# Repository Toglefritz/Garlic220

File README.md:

# Garlic220
The Garlic220 is an LED matrix for your NZXT H500 PC case featuring a 10 x 22 grid of WS2812B addressable LEDs (for 220 LEDs in total, hense the number in the name). The matrix, once mounted on a 3D printed frame with an acrylic diffuser, creates a grid of pixel-like lights. Using a bespoke Android app, the color of every pixel in the display can be controlled, allowing the Garlic220 to display any design you'd like.

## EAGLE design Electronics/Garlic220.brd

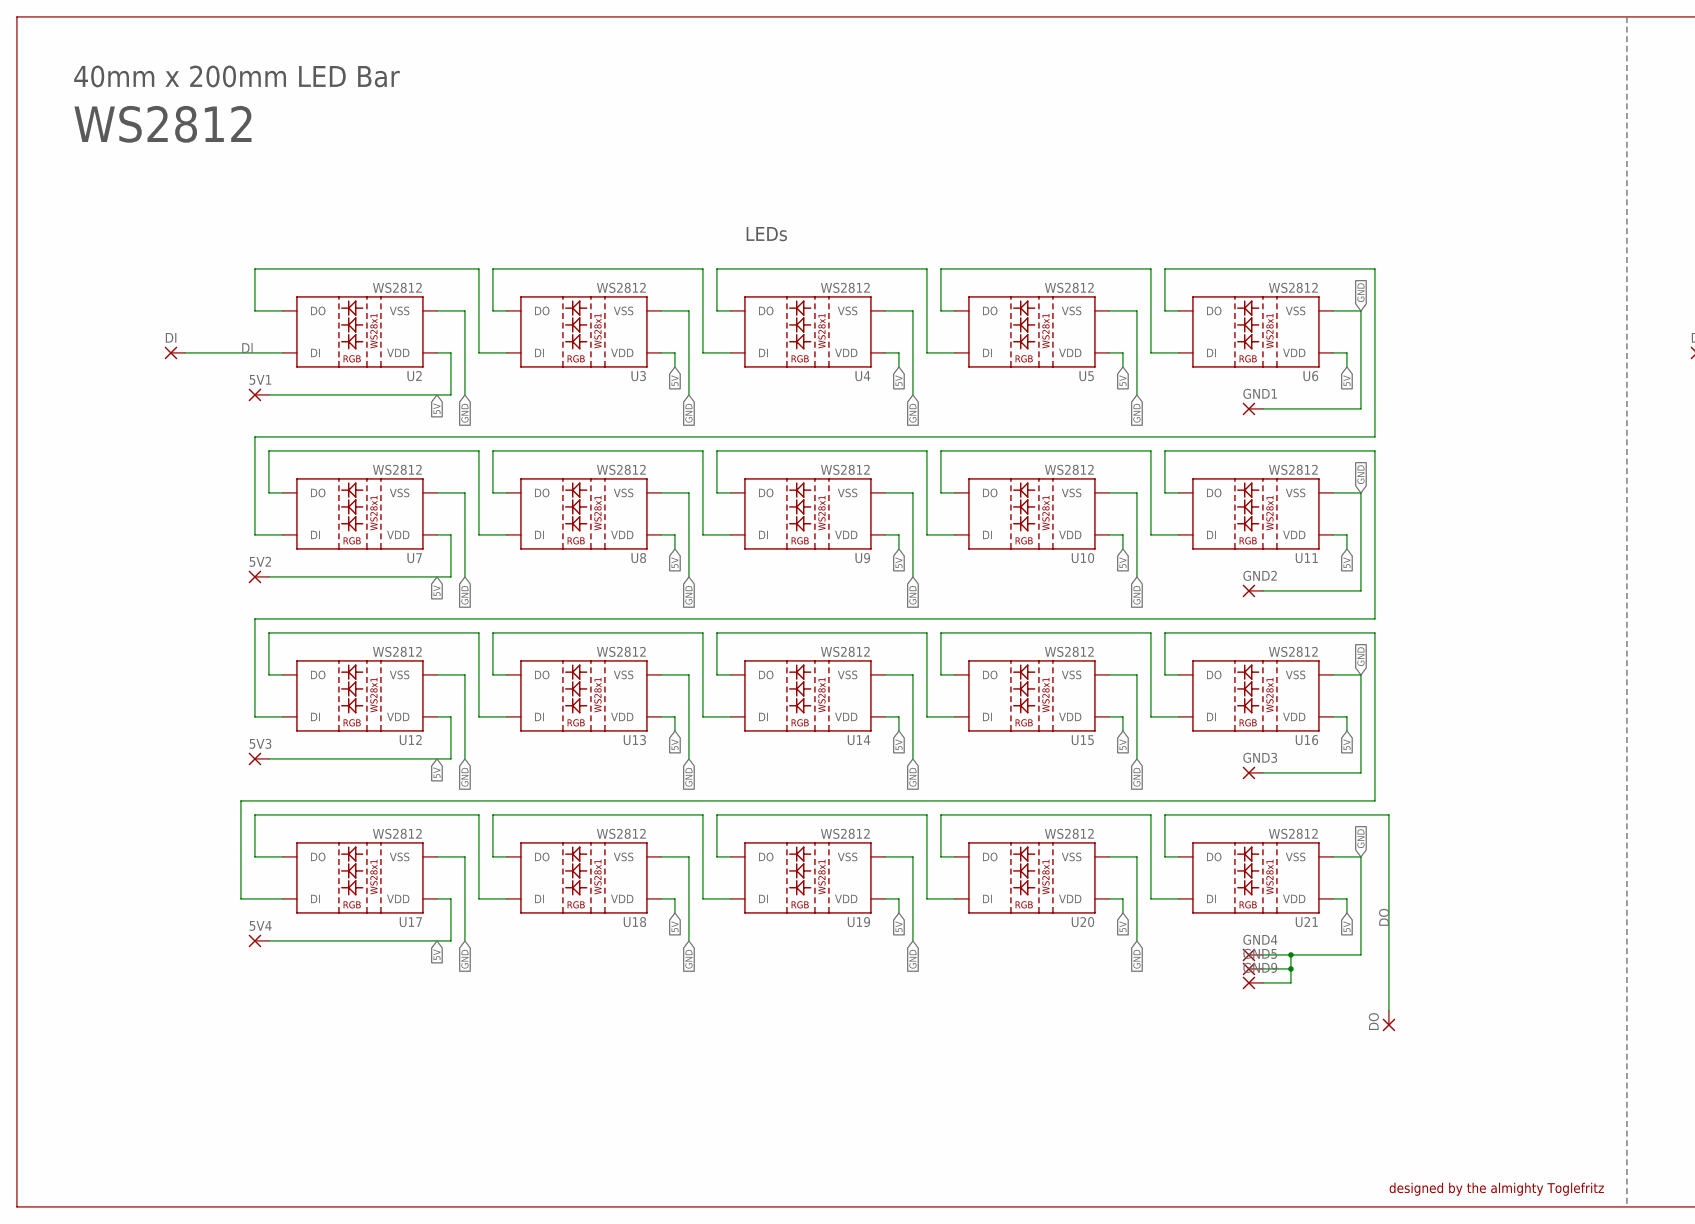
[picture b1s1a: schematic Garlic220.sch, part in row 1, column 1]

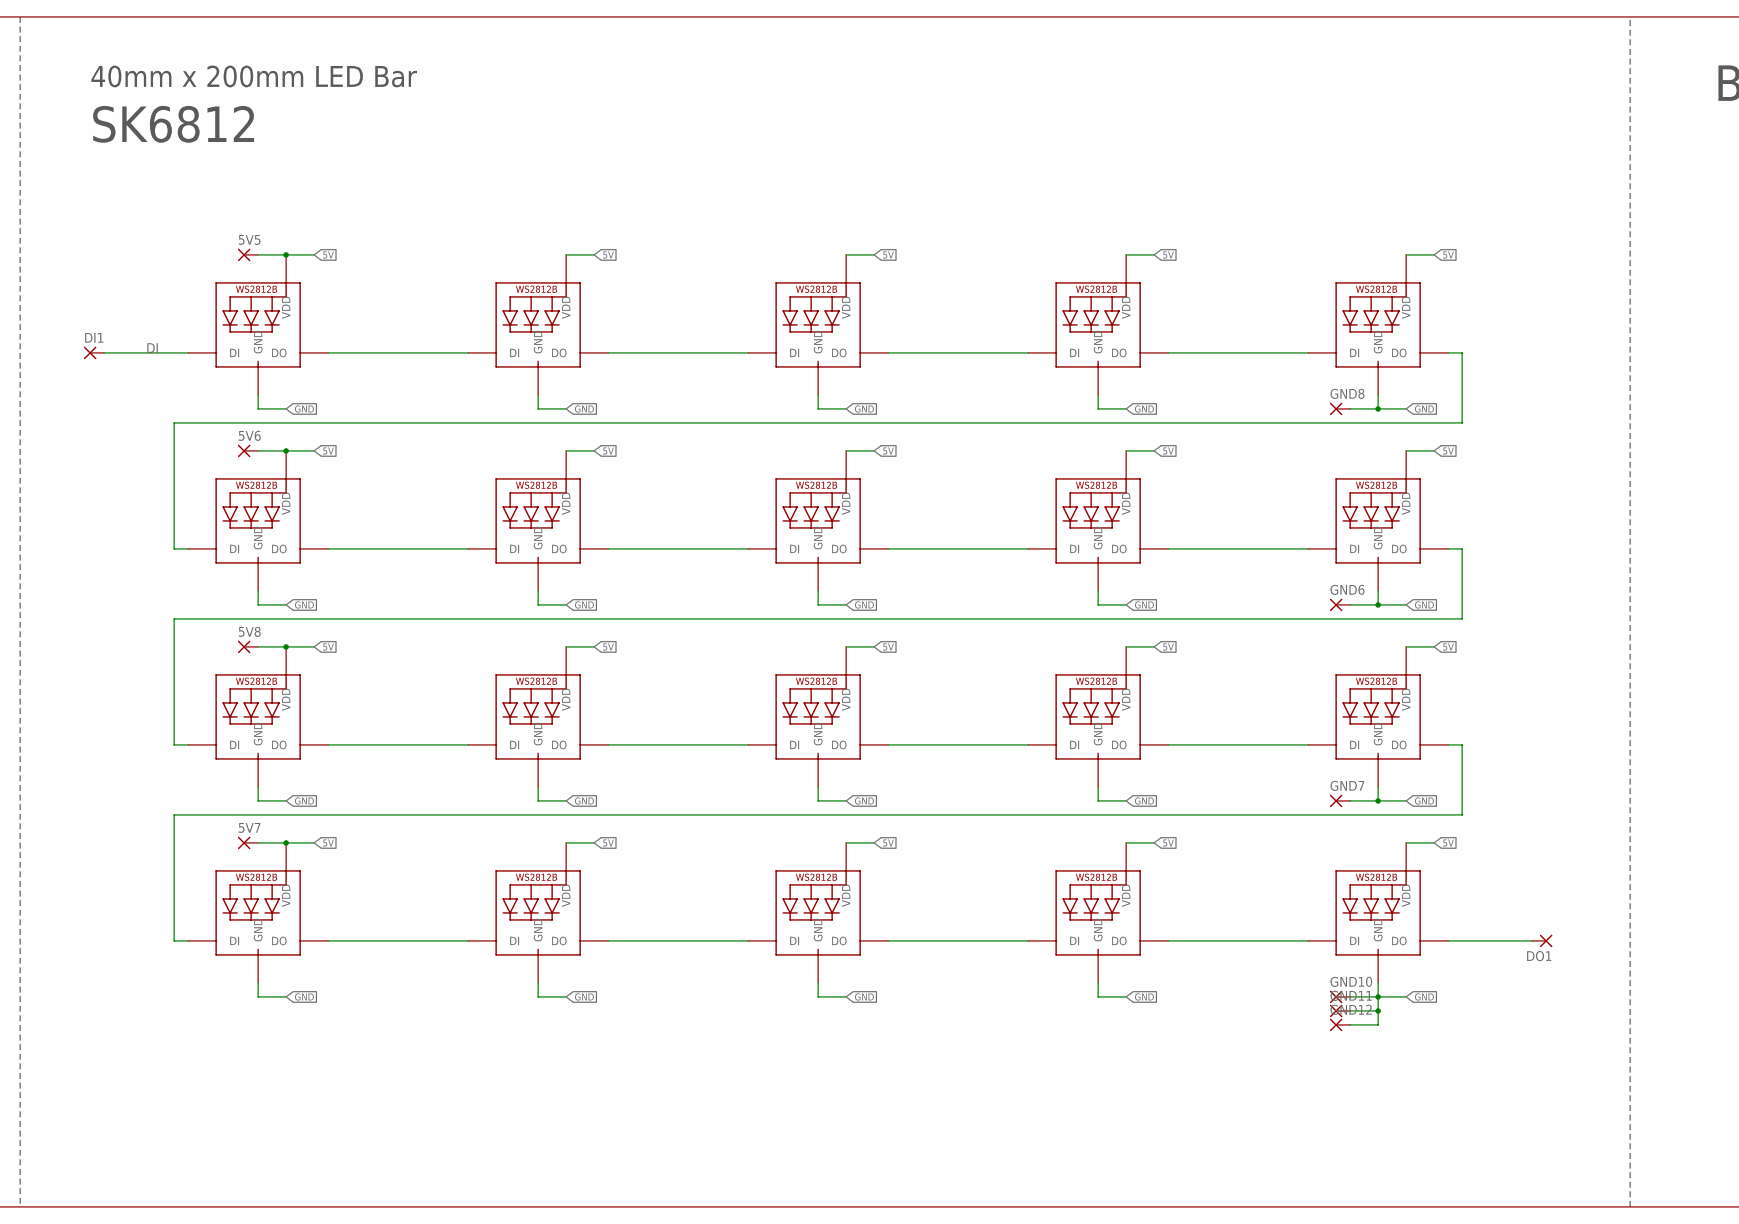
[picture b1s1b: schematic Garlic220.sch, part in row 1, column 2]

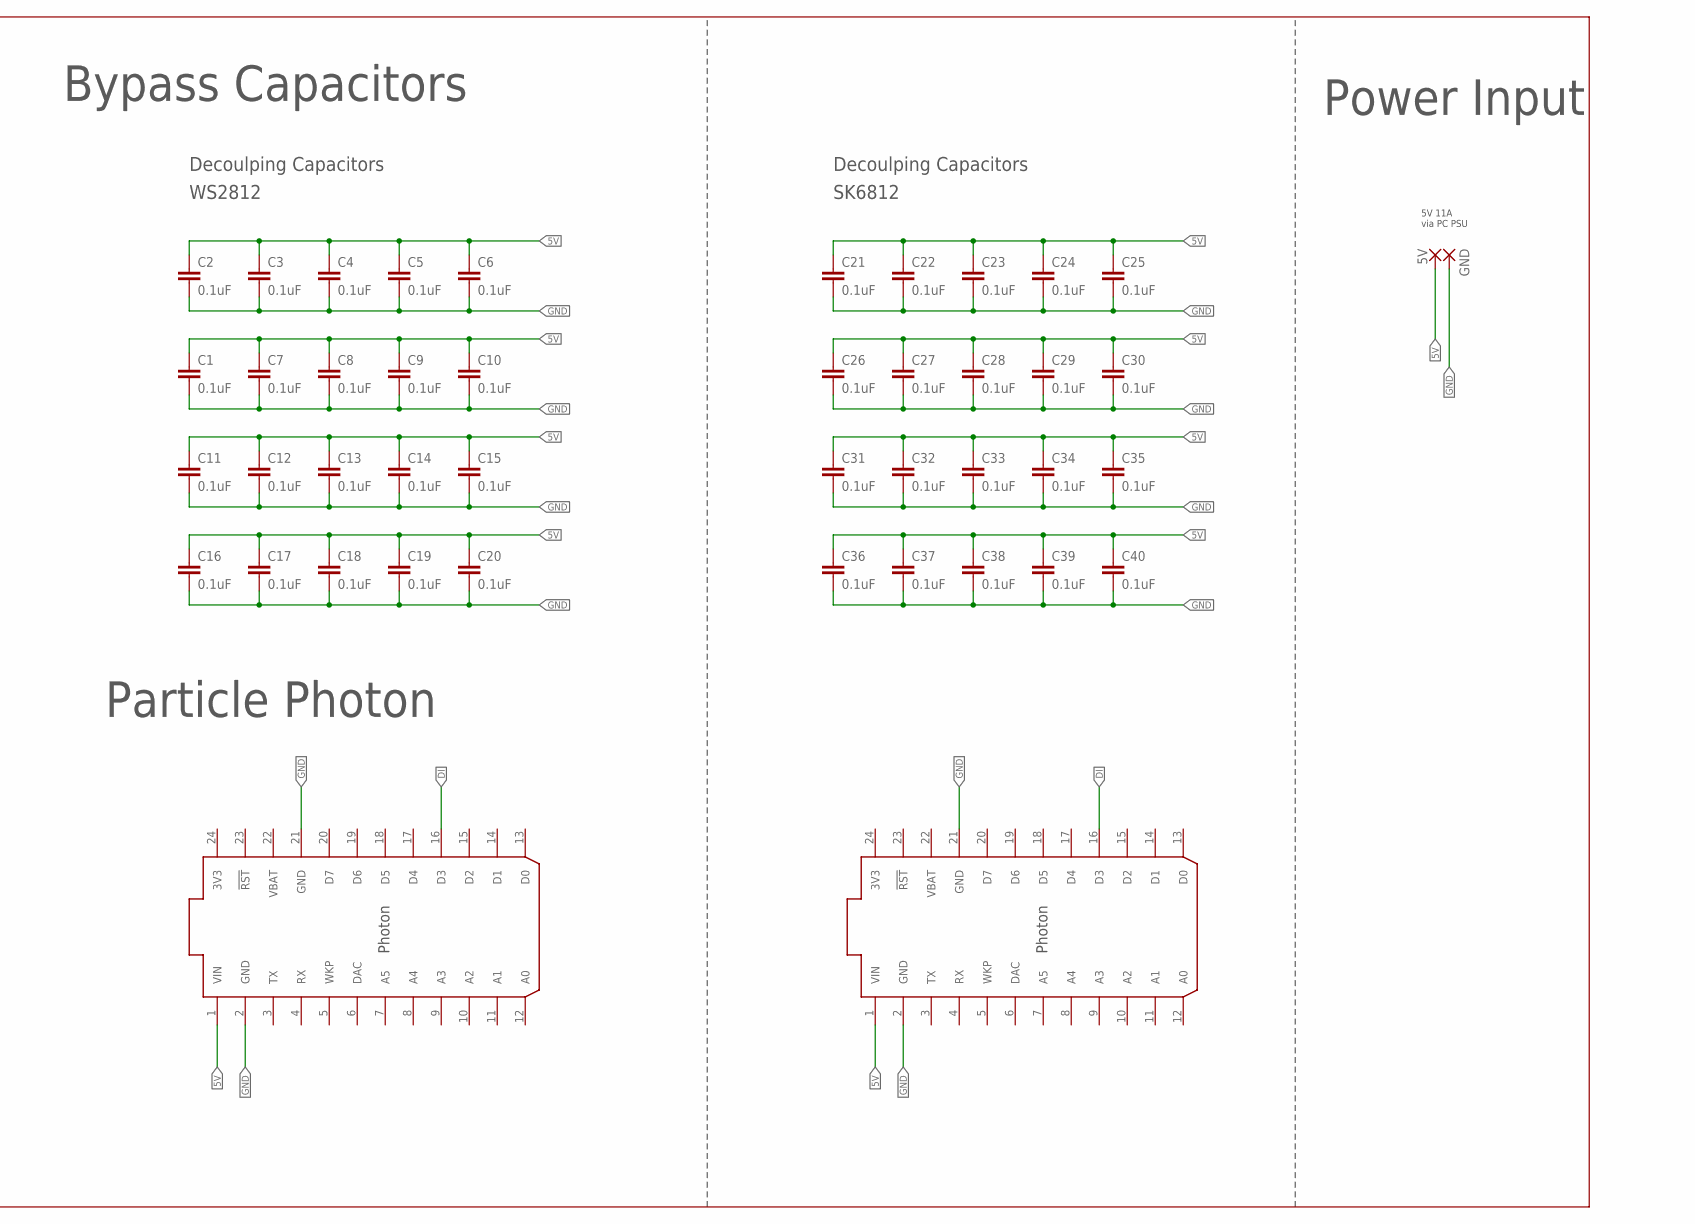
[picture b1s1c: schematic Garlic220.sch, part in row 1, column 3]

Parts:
5V: 3,81/1,1
5V1, 5V2, 5V3, 5V4, 5V5, 5V6, 5V7, 5V8: SMD5; SMD2,54-5,08
C1, C2, C3, C4, C5, C6, C7, C8, C9, C10, C11, C12, C13, C14, C15, C16, C17, C18, C19, C20, C21, C22, C23, C24, C25, C26, C27, C28, C29, C30, C31, C32, C33, C34, C35, C36, C37, C38, C39, C40: 0.1uF; 0805
DI, DI1: SMD5; SMD2,54-5,08
DO, DO1: SMD5; SMD2,54-5,08
GND: 3,81/1,1
GND1, GND2, GND3, GND4, GND5, GND6, GND7, GND8, GND9, GND10, GND11, GND12: SMD5; SMD2,54-5,08
LED21, LED22, LED23, LED24, LED25, LED26, LED27, LED28, LED29, LED30, LED31, LED32, LED33, LED34, LED35, LED36, LED37, LED38, LED39, LED40: WS2812B5050; WS2812B
U2, U3, U4, U5, U6, U7, U8, U9, U10, U11, U12, U13, U14, U15, U16, U17, U18, U19, U20, U21: WS2812; LED-TRICOLOR-5050-IC
U$1, U$2: PHOTON_SMD

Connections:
3V3: U$1.24 (3V3), U$2.24 (3V3)
5V: 5V.1, 5V1.1, 5V2.1, 5V3.1, 5V4.1, 5V5.1, 5V6.1, 5V7.1, 5V8.1, C1.1, C2.1, C3.1, C4.1, C5.1, C6.1, C7.1, C8.1, C9.1, C10.1, C11.1, C12.1, C13.1, C14.1, C15.1, C16.1, C17.1, C18.1, C19.1, C20.1, C21.1, C22.1, C23.1, C24.1, C25.1, C26.1, C27.1, C28.1, C29.1, C30.1, C31.1, C32.1, C33.1, C34.1, C35.1, C36.1, C37.1, C38.1, C39.1, C40.1, LED21.1-VDD (VDD), LED22.1-VDD (VDD), LED23.1-VDD (VDD), LED24.1-VDD (VDD), LED25.1-VDD (VDD), LED26.1-VDD (VDD), LED27.1-VDD (VDD), LED28.1-VDD (VDD), LED29.1-VDD (VDD), LED30.1-VDD (VDD), LED31.1-VDD (VDD), LED32.1-VDD (VDD), LED33.1-VDD (VDD), LED34.1-VDD (VDD), LED35.1-VDD (VDD), LED36.1-VDD (VDD), LED37.1-VDD (VDD), LED38.1-VDD (VDD), LED39.1-VDD (VDD), LED40.1-VDD (VDD), U2.3 (VDD), U2.5 (VDD), U3.3 (VDD), U3.5 (VDD), U4.3 (VDD), U4.5 (VDD), U5.3 (VDD), U5.5 (VDD), U6.3 (VDD), U6.5 (VDD), U7.3 (VDD), U7.5 (VDD), U8.3 (VDD), U8.5 (VDD), U9.3 (VDD), U9.5 (VDD), U10.3 (VDD), U10.5 (VDD), U11.3 (VDD), U11.5 (VDD), U12.3 (VDD), U12.5 (VDD), U13.3 (VDD), U13.5 (VDD), U14.3 (VDD), U14.5 (VDD), U15.3 (VDD), U15.5 (VDD), U16.3 (VDD), U16.5 (VDD), U17.3 (VDD), U17.5 (VDD), U18.3 (VDD), U18.5 (VDD), U19.3 (VDD), U19.5 (VDD), U20.3 (VDD), U20.5 (VDD), U21.3 (VDD), U21.5 (VDD), U$1.1 (VIN), U$2.1 (VIN)
DI: DI.1, DI1.1, LED21.4-DIN (DI), U2.2 (DI), U$1.16 (D3), U$2.16 (D3)
DI1: U16.1 (DO), U17.2 (DI)
DO: DO.1, U21.1 (DO)
GND: C1.2, C2.2, C3.2, C4.2, C5.2, C6.2, C7.2, C8.2, C9.2, C10.2, C11.2, C12.2, C13.2, C14.2, C15.2, C16.2, C17.2, C18.2, C19.2, C20.2, C21.2, C22.2, C23.2, C24.2, C25.2, C26.2, C27.2, C28.2, C29.2, C30.2, C31.2, C32.2, C33.2, C34.2, C35.2, C36.2, C37.2, C38.2, C39.2, C40.2, GND.1, GND1.1, GND2.1, GND3.1, GND4.1, GND5.1, GND6.1, GND7.1, GND8.1, GND9.1, GND10.1, GND11.1, GND12.1, LED21.3-GND (GND), LED22.3-GND (GND), LED23.3-GND (GND), LED24.3-GND (GND), LED25.3-GND (GND), LED26.3-GND (GND), LED27.3-GND (GND), LED28.3-GND (GND), LED29.3-GND (GND), LED30.3-GND (GND), LED31.3-GND (GND), LED32.3-GND (GND), LED33.3-GND (GND), LED34.3-GND (GND), LED35.3-GND (GND), LED36.3-GND (GND), LED37.3-GND (GND), LED38.3-GND (GND), LED39.3-GND (GND), LED40.3-GND (GND), U2.6 (VSS), U3.6 (VSS), U4.6 (VSS), U5.6 (VSS), U6.6 (VSS), U7.6 (VSS), U8.6 (VSS), U9.6 (VSS), U10.6 (VSS), U11.6 (VSS), U12.6 (VSS), U13.6 (VSS), U14.6 (VSS), U15.6 (VSS), U16.6 (VSS), U17.6 (VSS), U18.6 (VSS), U19.6 (VSS), U20.6 (VSS), U21.6 (VSS), U$1.2 (GND), U$1.21 (GND), U$2.2 (GND), U$2.21 (GND)
unnamed: U2.1 (DO), U3.2 (DI)
unnamed: U3.1 (DO), U4.2 (DI)
unnamed: U4.1 (DO), U5.2 (DI)
unnamed: U7.1 (DO), U8.2 (DI)
unnamed: U8.1 (DO), U9.2 (DI)
unnamed: U9.1 (DO), U10.2 (DI)
unnamed: U6.1 (DO), U7.2 (DI)
unnamed: U12.1 (DO), U13.2 (DI)
unnamed: U13.1 (DO), U14.2 (DI)
unnamed: U14.1 (DO), U15.2 (DI)
unnamed: U11.1 (DO), U12.2 (DI)
unnamed: U5.1 (DO), U6.2 (DI)
unnamed: U17.1 (DO), U18.2 (DI)
unnamed: U15.1 (DO), U16.2 (DI)
unnamed: U18.1 (DO), U19.2 (DI)
unnamed: U10.1 (DO), U11.2 (DI)
unnamed: U19.1 (DO), U20.2 (DI)
unnamed: LED21.2-DOUT (DO), LED22.4-DIN (DI)
unnamed: LED22.2-DOUT (DO), LED23.4-DIN (DI)
unnamed: LED23.2-DOUT (DO), LED24.4-DIN (DI)
unnamed: LED24.2-DOUT (DO), LED25.4-DIN (DI)
unnamed: LED25.2-DOUT (DO), LED26.4-DIN (DI)
unnamed: LED26.2-DOUT (DO), LED27.4-DIN (DI)
unnamed: LED27.2-DOUT (DO), LED28.4-DIN (DI)
unnamed: LED28.2-DOUT (DO), LED29.4-DIN (DI)
unnamed: U20.1 (DO), U21.2 (DI)
unnamed: LED29.2-DOUT (DO), LED30.4-DIN (DI)
unnamed: LED30.2-DOUT (DO), LED31.4-DIN (DI)
unnamed: LED31.2-DOUT (DO), LED32.4-DIN (DI)
unnamed: LED32.2-DOUT (DO), LED33.4-DIN (DI)
unnamed: LED33.2-DOUT (DO), LED34.4-DIN (DI)
unnamed: LED34.2-DOUT (DO), LED35.4-DIN (DI)
unnamed: LED35.2-DOUT (DO), LED36.4-DIN (DI)
unnamed: LED36.2-DOUT (DO), LED37.4-DIN (DI)
unnamed: LED37.2-DOUT (DO), LED38.4-DIN (DI)
unnamed: LED38.2-DOUT (DO), LED39.4-DIN (DI)
unnamed: LED39.2-DOUT (DO), LED40.4-DIN (DI)
unnamed: DO1.1, LED40.2-DOUT (DO)
VBAT: U$1.22 (VBAT), U$2.22 (VBAT)

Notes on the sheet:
designed by the almighty Toglefritz
LEDs
40mm x 200mm LED Bar
WS2812
SK6812
Bypass Capacitors
Decoulping Capacitors
Particle Photon
Power Input
5V 11A via PC PSU

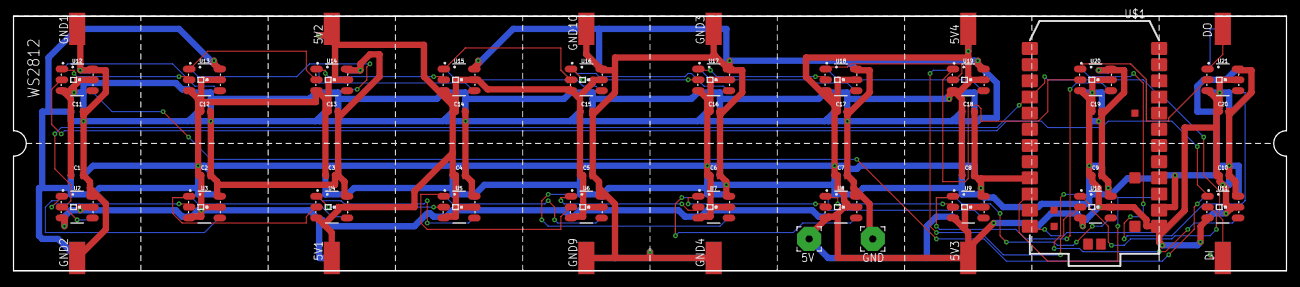
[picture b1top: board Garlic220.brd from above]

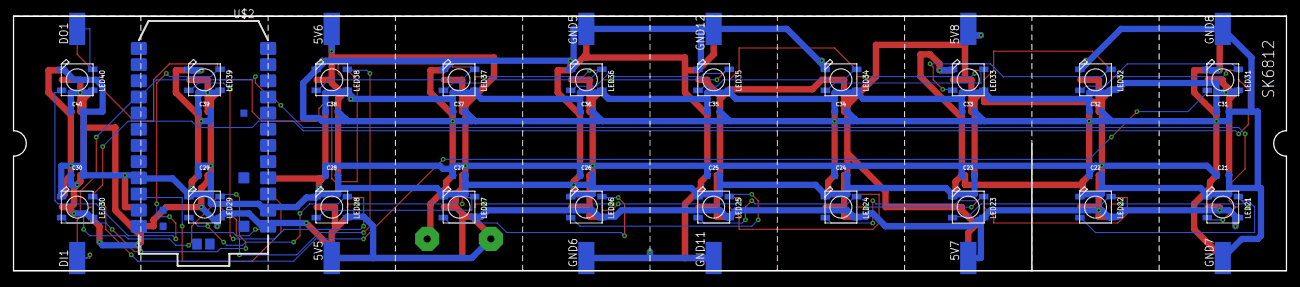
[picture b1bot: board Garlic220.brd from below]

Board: 4 copper layers, 200.0 x 40.0 mm, 108 parts (53 on the bottom side), 45 nets.

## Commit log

2020-07-25 Initial commit. Added electronics and CAD design files, reference design files.
2020-07-25 Added Seeed Studio Gerbers.
2020-07-26 Created README.md

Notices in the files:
parts and their libraries:
SparkFun-LED: Licensing: Creative Commons ShareAlike 4.0 International - https://creativecommons.org/licenses/by-sa/4.0
Particle-Devices: Licensing: Designed by Particle.
